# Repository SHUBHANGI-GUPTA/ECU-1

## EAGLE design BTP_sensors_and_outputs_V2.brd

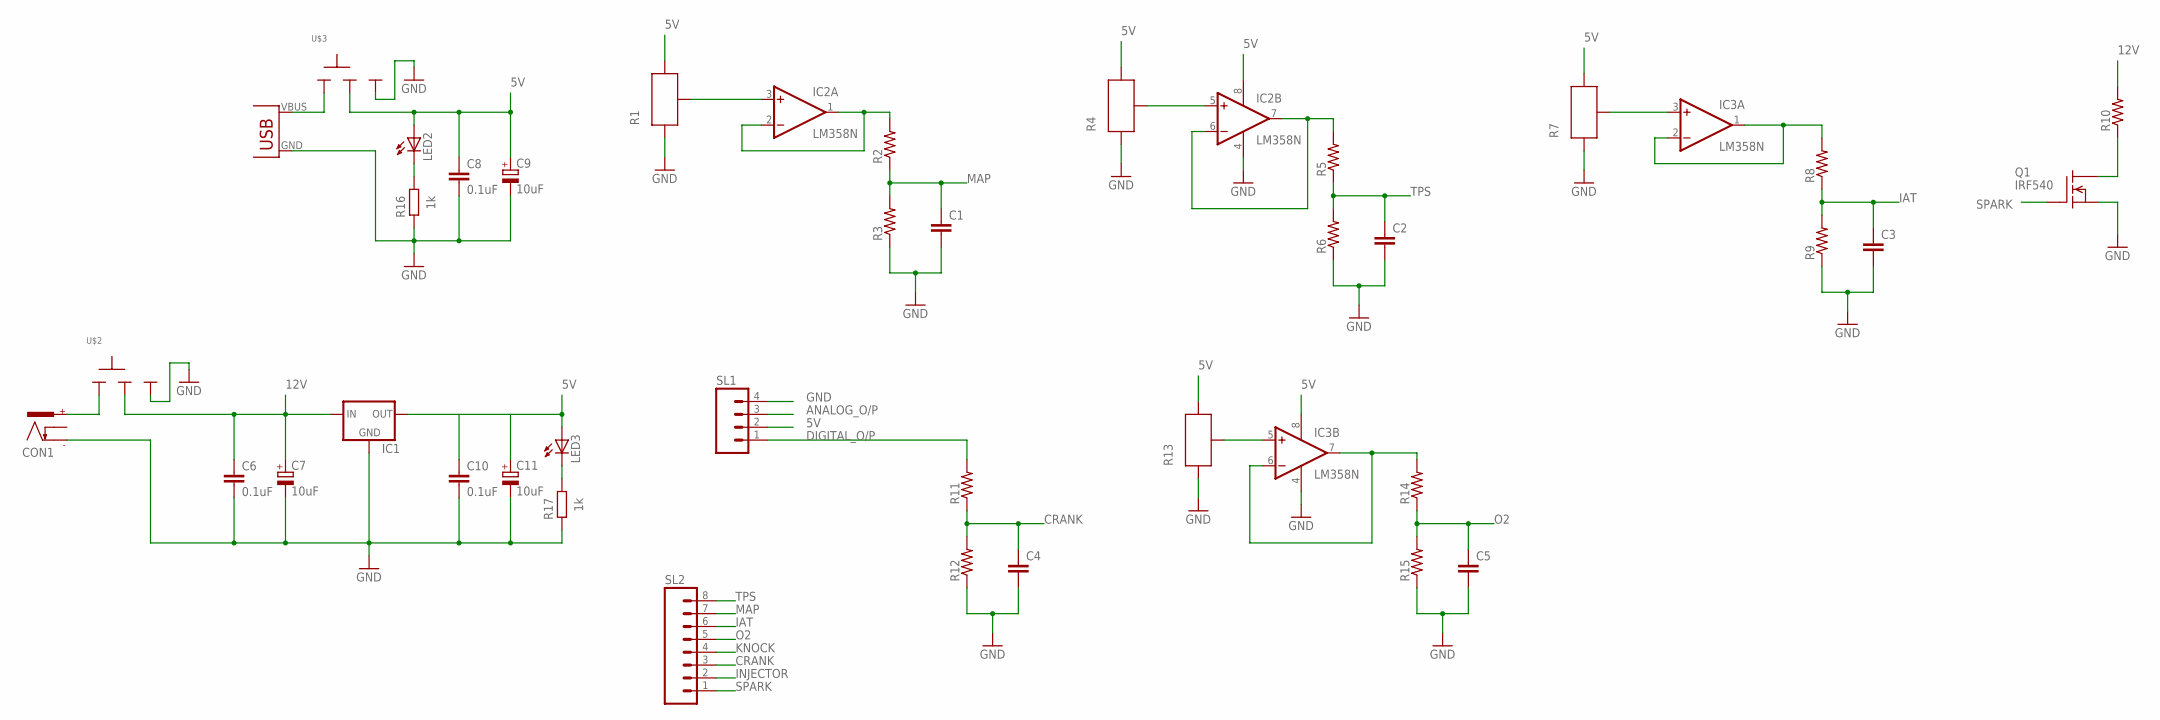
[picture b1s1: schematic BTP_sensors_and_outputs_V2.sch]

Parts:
C1, C2, C3, C4, C5: CAPACITOR-NON_POLAR025-025X050; C025-025X050
C6, C8, C10: 0.1uF; C025-025X050
C7, C9, C11: 10uF; E2,5-5
CON1: POWER_CON; NEB21R
IC1: V_REG_78XXSINK; TO220-IGO
IC2, IC3: LM358N; DIL08
LED2, LED3: LED3MM
Q1: IRF540; TO220
R1, R4, R7, R13: POTNORMAL; RJ9W
R2, R3, R5, R6, R8, R9, R10, R11, R12, R14, R15: RESISTOR-1/8W; 0204/7
R16, R17: 1k; 0204/7
SL1: M04; 04P
SL2: M08; 08P
U$2, U$3: SLIDESWITCH-BIG; BIGSWITCH
U$4: USB-POWER; MINI-USB-POWER

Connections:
5V: C8.1, C9.+, IC1.OUT, IC2.8 (V+), IC3.8 (V+), LED2.A, LED3.A, R1.A, R4.A, R7.A, R13.A, SL1.2, U$3.2
12V: C6.1, C7.+, IC1.IN, R10.2, U$2.2
12V1: C10.1, C11.+
ANALOG_O/P: SL1.3
CRANK: C4.1, R11.1, R12.2, SL2.3
DIGITAL_O/P: R11.2, SL1.1
GND: C1.2, C2.2, C3.2, C4.2, C5.2, C6.2, C7.-, C8.2, C9.-, C10.2, C11.-, CON1.-, IC1.GND, IC2.4 (V-), IC3.4 (V-), Q1.3 (S), R1.E, R3.1, R4.E, R6.1, R7.E, R9.1, R12.1, R13.E, R15.1, R16.2, R17.2, SL1.4, U$2.3, U$3.3, U$4.GND
IAT: C3.1, R8.1, R9.2, SL2.6
INJECTOR: SL2.2
KNOCK: SL2.4
MAP: C1.1, R2.1, R3.2, SL2.7
unnamed: IC2.5 (+IN), R4.S
unnamed: IC3.3 (+IN), R7.S
unnamed: Q1.2 (D), R10.1
unnamed: IC3.5 (+IN), R13.S
unnamed: IC2.3 (+IN), R1.S
unnamed: CON1.+, U$2.1
unnamed: U$3.1, U$4.VBUS (VCC)
unnamed: LED2.K (C), R16.1
unnamed: LED3.K (C), R17.1
unnamed: IC2.1 (OUT), IC2.2 (-IN), R2.2
unnamed: IC2.6 (-IN), IC2.7 (OUT), R5.2
unnamed: IC3.1 (OUT), IC3.2 (-IN), R8.2
unnamed: IC3.6 (-IN), IC3.7 (OUT), R14.2
O2: C5.1, R14.1, R15.2, SL2.5
SPARK: Q1.1 (G), SL2.1
TPS: C2.1, R5.1, R6.2, SL2.8

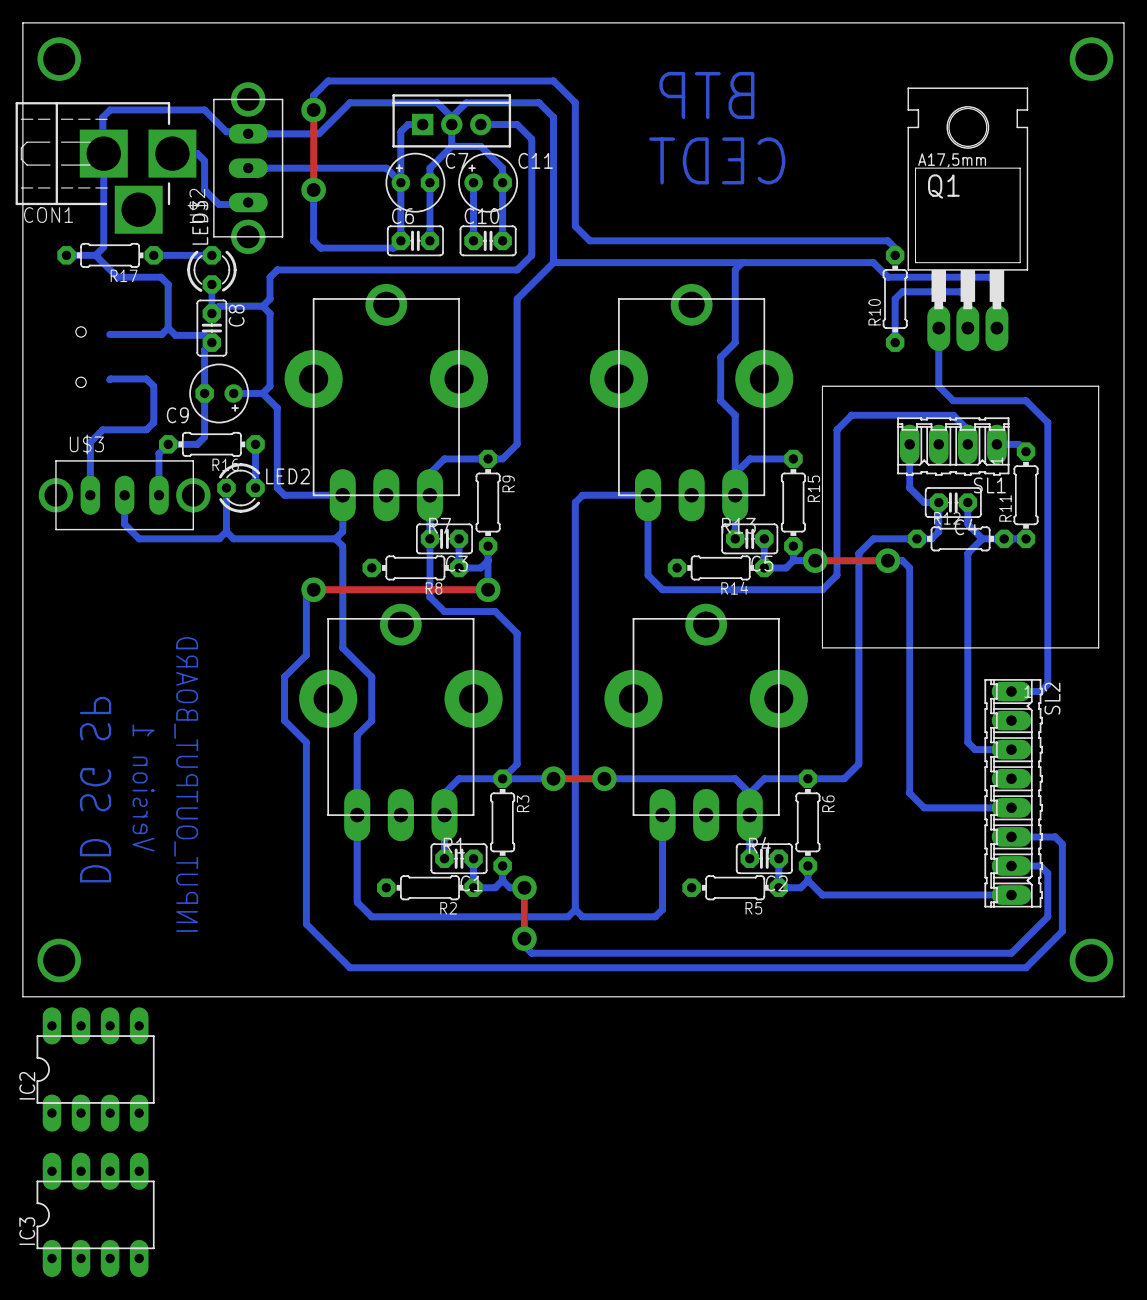
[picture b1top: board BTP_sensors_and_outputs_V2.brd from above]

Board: 2 copper layers, 96.2 x 85.1 mm, 40 parts (1 on the bottom side), 24 nets.

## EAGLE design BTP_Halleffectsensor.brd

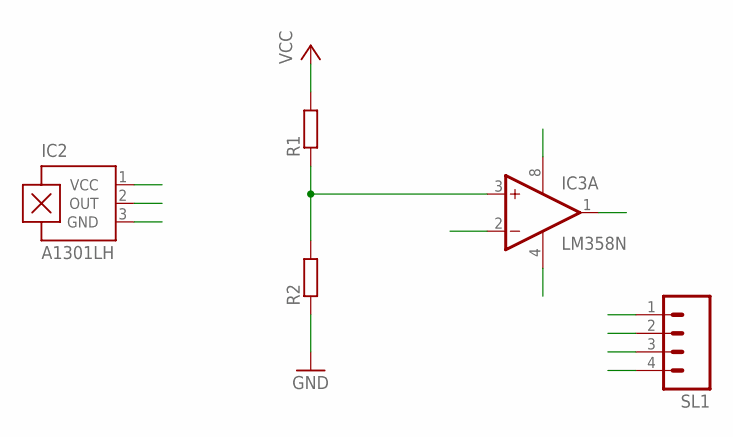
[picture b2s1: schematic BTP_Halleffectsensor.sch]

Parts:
IC2: A1301LH; SOT23-W
IC3: LM358N; DIL08
R1, R2: R-EU_0204/7; 0204/7
SL1: M04; 04P

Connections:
DOUT: IC3.1 (OUT), SL1.4
GND: IC2.3 (GND), IC3.4 (V-), R2.1, SL1.1
unnamed: IC3.3 (+IN), R1.1, R2.2
OUT: IC2.2 (OUT), IC3.2 (-IN), SL1.2
VCC: IC2.1 (VCC), IC3.8 (V+), R1.2, SL1.3

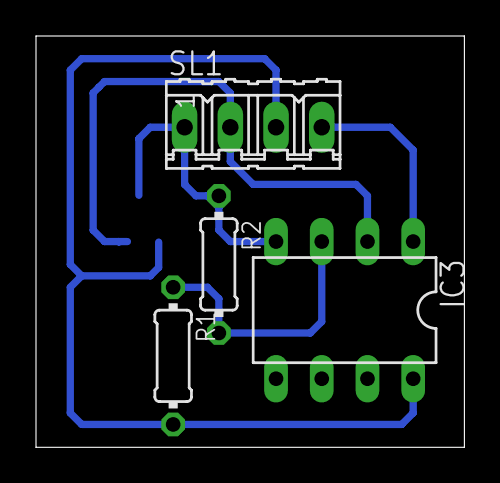
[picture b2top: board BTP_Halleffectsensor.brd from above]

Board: 2 copper layers, 23.8 x 22.9 mm, 5 parts (1 on the bottom side), 5 nets.

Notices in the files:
parts and their libraries:
SparkFun-PowerIC: Licensing: Creative Commons ShareAlike 4.0 International - https://creativecommons.org/licenses/by-sa/4.0
